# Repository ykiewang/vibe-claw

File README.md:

# vibe-claw

专为 vibe coding 设计的爪形人体工学键盘。

## 项目结构

```
vibe-claw/
├── pcb/        # KiCad 工程文件
└── README.md
```

## PCB 设计

使用 [KiCad](https://www.kicad.org/) 设计，工程文件位于 `pcb/` 目录。

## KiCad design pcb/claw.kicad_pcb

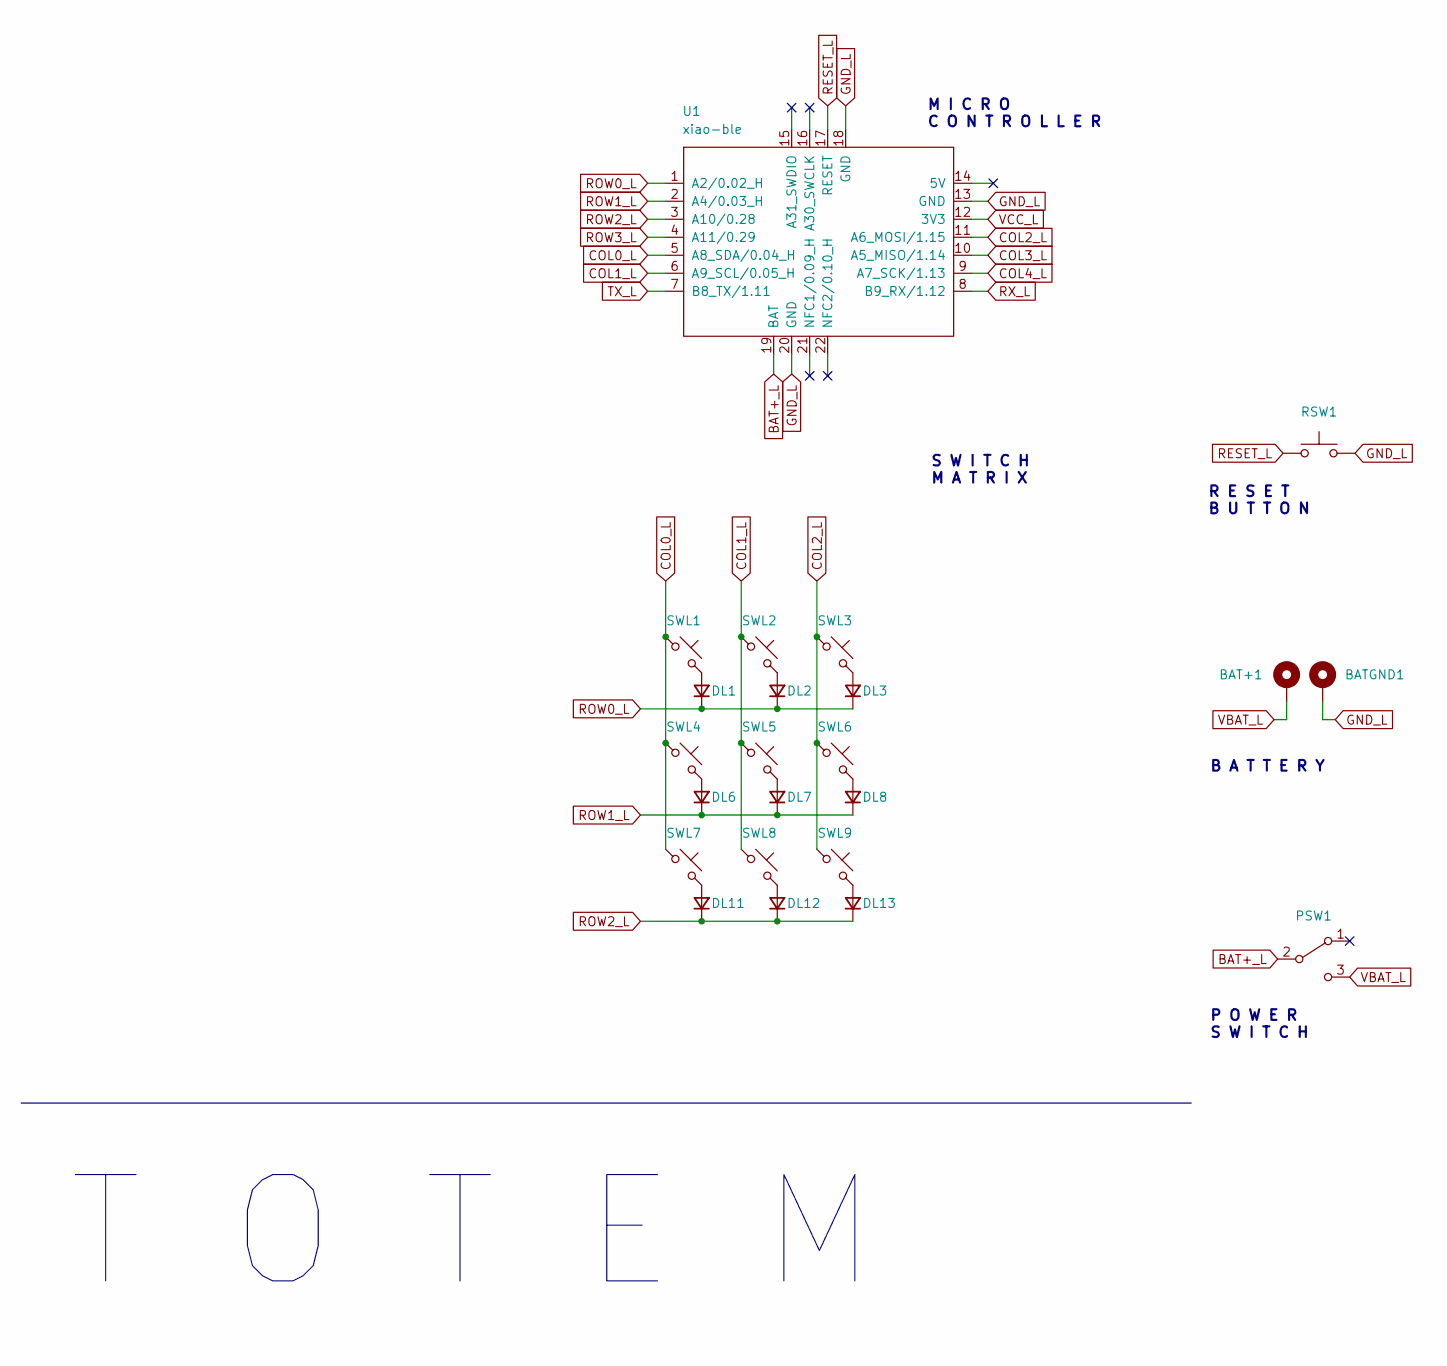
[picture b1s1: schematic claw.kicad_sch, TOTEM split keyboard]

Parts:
BAT+1: +; BatteryPad
BATGND1: -; BatteryPad
DL1, DL2, DL3, DL6, DL7, DL8, DL11, DL12, DL13: D_Small; Diode_SOD123
PSW1: SW_SPDT; MSK12C02
RSW1: SW_Push; SKHLLCA010
SWL1, SWL2, SWL3, SWL4, SWL5, SWL6, SWL7, SWL8, SWL9: SW_Push_45deg; Kailh_socket_PG1350_optional
U1: xiao-ble; xiao-ble-smd-cutout

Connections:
BAT+_L: PSW1.2 (B), U1.19 (BAT)
COL0_L: SWL1.1, SWL4.1, SWL7.1, U1.5 (A8_SDA/0.04_H)
COL1_L: SWL2.1, SWL5.1, SWL8.1, U1.6 (A9_SCL/0.05_H)
COL2_L: SWL3.1, SWL6.1, SWL9.1, U1.11 (A6_MOSI/1.15)
COL3_L: U1.10 (A5_MISO/1.14)
COL4_L: U1.9 (A7_SCK/1.13)
GND_L: BATGND1.1, RSW1.2, U1.13 (GND), U1.18 (GND), U1.20 (GND)
unnamed: DL1.2 (A), SWL1.2
unnamed: DL2.2 (A), SWL2.2
unnamed: DL3.2 (A), SWL3.2
unnamed: DL6.2 (A), SWL4.2
unnamed: DL7.2 (A), SWL5.2
unnamed: DL8.2 (A), SWL6.2
unnamed: DL11.2 (A), SWL7.2
unnamed: DL12.2 (A), SWL8.2
unnamed: DL13.2 (A), SWL9.2
RESET_L: RSW1.1, U1.17 (RESET)
ROW0_L: DL1.1 (K), DL2.1 (K), DL3.1 (K), U1.1 (A2/0.02_H)
ROW1_L: DL6.1 (K), DL7.1 (K), DL8.1 (K), U1.2 (A4/0.03_H)
ROW2_L: DL11.1 (K), DL12.1 (K), DL13.1 (K), U1.3 (A10/0.28)
ROW3_L: U1.4 (A11/0.29)
RX_L: U1.8 (B9_RX/1.12)
TX_L: U1.7 (B8_TX/1.11)
VBAT_L: BAT+1.1, PSW1.3 (C)
VCC_L: U1.12 (3V3)

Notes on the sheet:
R E S E T B U T T O N
S W I T C H M A T R I X
P O W E R S W I T C H
T O T E M
B A T T E R Y
M I C R O C O N T R O L L E R

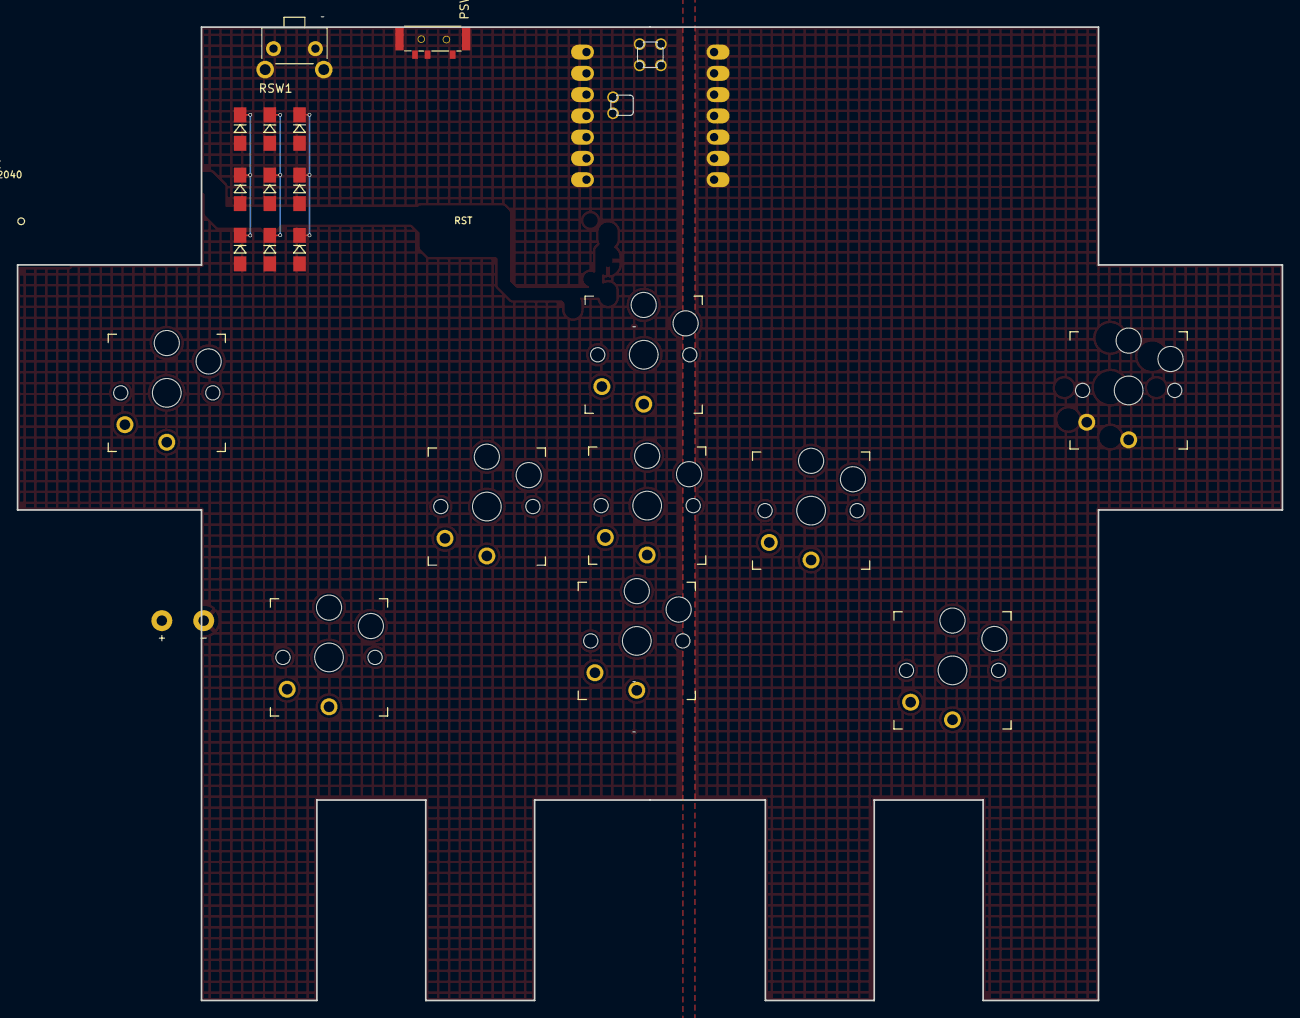
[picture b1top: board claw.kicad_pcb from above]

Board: 2 copper layers, 151.1 x 117.5 mm, 23 parts (0 on the bottom side), 19 nets.

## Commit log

2026-04-03 Initial commit: claw keyboard KiCad project
2026-04-03 reorganize: move KiCad files to pcb/, add README
2026-04-03 remove .DS_Store, add to .gitignore
